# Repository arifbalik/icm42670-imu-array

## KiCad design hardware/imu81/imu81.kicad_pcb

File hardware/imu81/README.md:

# IMU81 Array Module

<div align="center">

</div>

## Overview

A compact 8-sensor IMU array module featuring ICM-42670-P sensors with STM32 microcontroller for high-performance and very high-accuracy motion sensing applications.

## Key Features

### IMU Sensors

- **8x ICM-42670-P** 6-axis MEMS motion tracking devices
- High-performance 3-axis gyroscope and 3-axis accelerometer  
- Shared SPI bus with individual interrupt lines
- **Gyroscope Range**: ±250, ±500, ±1000, ±2000 dps
- **Accelerometer Range**: ±2, ±4, ±8, ±16 g

### Microcontroller

- **STM32U031K8** ARM Cortex-M0+ ultra-low-power MCU
- 64KB Flash memory, 12KB SRAM
- Ultra-low power consumption

### Interface & Connectivity

- **Dual 6-pin headers** for external connections
- SPI interface for sensor communication
- I2C/UART interface for external communication
- One interrupt line for the host
- Interrupt signals from all 8 IMU sensors

## Technical Specifications

### Dimensions

- **Size**: 16mm x 17mm
- **Weight**: 5g

### Power Supply

- **Operating Voltage**: 1.8V - 3.3V
- **Power Consumption**: Ultra-low power design optimized for battery operation

#### Individual Power Consumption

- **ICM-42670-P (Single)**: 0.55mA (active), 3.5µA (sleep)
- **STM32U031K8**: 4mA (active), 16nA (sleep)

## Operating Conditions

- **Temperature Range**: -40°C to +85°C
- **Humidity Range**: 0% to 100% (non-condensing)

## How To Build

To generate fabrication artifacts make sure you have [Docker](https://www.docker.com/) installed and running.

Then simply run;

```bash
make build
```

from the project root. This will generate an `output` directory containing the fabrication artifacts in the parent directory.

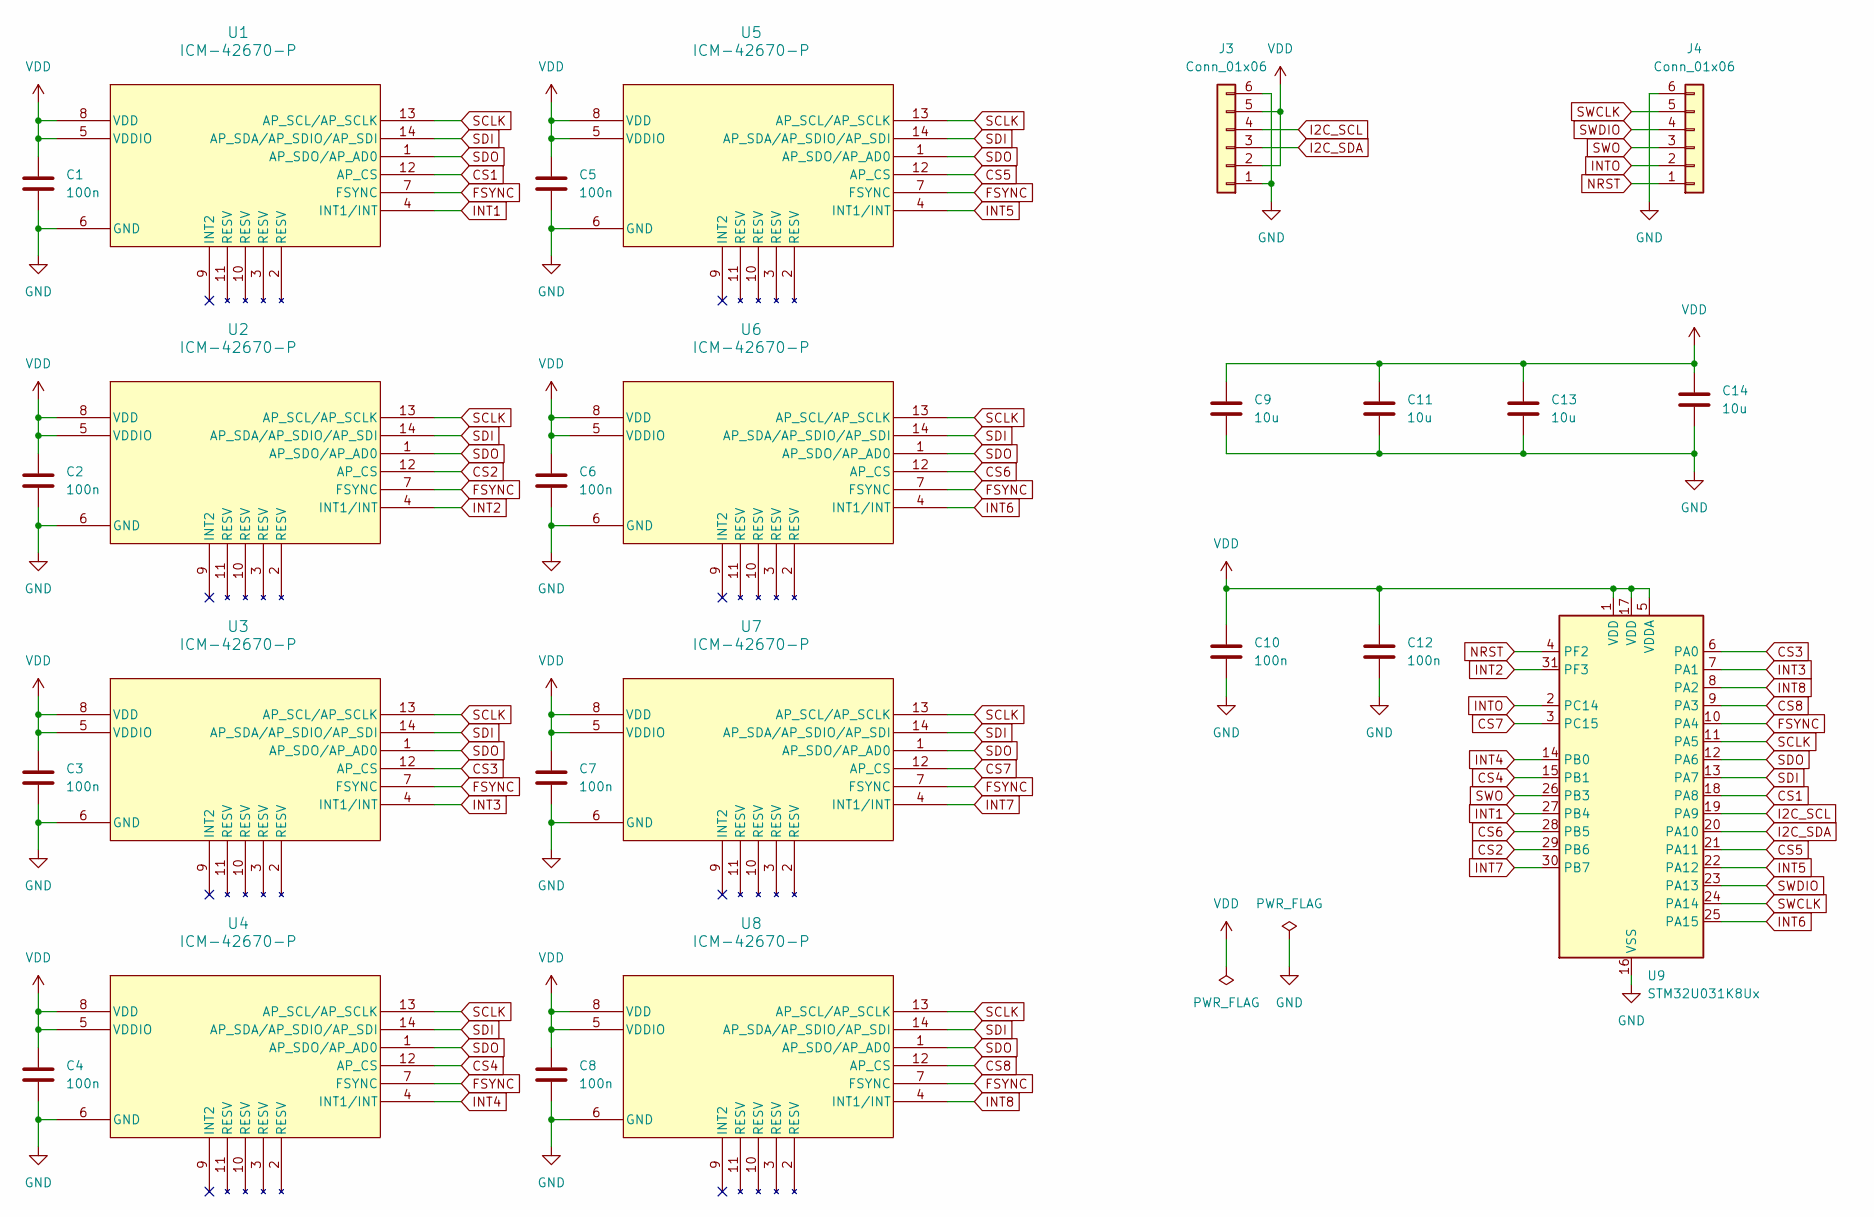
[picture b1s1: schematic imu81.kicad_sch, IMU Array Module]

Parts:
C1, C2, C3, C4, C5, C6, C7, C8, C10, C12: 100n; C_0201_0603Metric
C9, C11, C13, C14: 10u; C_0603_1608Metric
J3, J4: Conn_01x06; PinHeader_1x06_P2.54mm_Vertical
U1, U2, U3, U4, U5, U6, U7, U8: ICM-42670-P; LGA14_2.5X3X0.76_IVS
U9: STM32U031K8Ux; QFN-32-1EP_5x5mm_P0.5mm_EP3.45x3.45mm

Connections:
CS1: U1.12 (AP_CS), U9.18 (PA8)
CS2: U2.12 (AP_CS), U9.29 (PB6)
CS3: U3.12 (AP_CS), U9.6 (PA0)
CS4: U4.12 (AP_CS), U9.15 (PB1)
CS5: U5.12 (AP_CS), U9.21 (PA11)
CS6: U6.12 (AP_CS), U9.28 (PB5)
CS7: U7.12 (AP_CS), U9.3 (PC15)
CS8: U8.12 (AP_CS), U9.9 (PA3)
FSYNC: U1.7 (FSYNC), U2.7 (FSYNC), U3.7 (FSYNC), U4.7 (FSYNC), U5.7 (FSYNC), U6.7 (FSYNC), U7.7 (FSYNC), U8.7 (FSYNC), U9.10 (PA4)
GND: C1.2, C2.2, C3.2, C4.2, C5.2, C6.2, C7.2, C8.2, C9.2, C10.2, C11.2, C12.2, C13.2, C14.2, J3.1, J3.6, J4.6, U1.6 (GND), U2.6 (GND), U3.6 (GND), U4.6 (GND), U5.6 (GND), U6.6 (GND), U7.6 (GND), U8.6 (GND), U9.16 (VSS), U9.32 (VSS), U9.33 (VSS)
I2C_SCL: J3.4, U9.19 (PA9)
I2C_SDA: J3.3, U9.20 (PA10)
INT1: U1.4 (INT1/INT), U9.27 (PB4)
INT2: U2.4 (INT1/INT), U9.31 (PF3)
INT3: U3.4 (INT1/INT), U9.7 (PA1)
INT4: U4.4 (INT1/INT), U9.14 (PB0)
INT5: U5.4 (INT1/INT), U9.22 (PA12)
INT6: U6.4 (INT1/INT), U9.25 (PA15)
INT7: U7.4 (INT1/INT), U9.30 (PB7)
INT8: U8.4 (INT1/INT), U9.8 (PA2)
INTO: J4.2, U9.2 (PC14)
NRST: J4.1, U9.4 (PF2)
SCLK: U1.13 (AP_SCL/AP_SCLK), U2.13 (AP_SCL/AP_SCLK), U3.13 (AP_SCL/AP_SCLK), U4.13 (AP_SCL/AP_SCLK), U5.13 (AP_SCL/AP_SCLK), U6.13 (AP_SCL/AP_SCLK), U7.13 (AP_SCL/AP_SCLK), U8.13 (AP_SCL/AP_SCLK), U9.11 (PA5)
SDI: U1.14 (AP_SDA/AP_SDIO/AP_SDI), U2.14 (AP_SDA/AP_SDIO/AP_SDI), U3.14 (AP_SDA/AP_SDIO/AP_SDI), U4.14 (AP_SDA/AP_SDIO/AP_SDI), U5.14 (AP_SDA/AP_SDIO/AP_SDI), U6.14 (AP_SDA/AP_SDIO/AP_SDI), U7.14 (AP_SDA/AP_SDIO/AP_SDI), U8.14 (AP_SDA/AP_SDIO/AP_SDI), U9.13 (PA7)
SDO: U1.1 (AP_SDO/AP_AD0), U2.1 (AP_SDO/AP_AD0), U3.1 (AP_SDO/AP_AD0), U4.1 (AP_SDO/AP_AD0), U5.1 (AP_SDO/AP_AD0), U6.1 (AP_SDO/AP_AD0), U7.1 (AP_SDO/AP_AD0), U8.1 (AP_SDO/AP_AD0), U9.12 (PA6)
SWCLK: J4.5, U9.24 (PA14)
SWDIO: J4.4, U9.23 (PA13)
SWO: J4.3, U9.26 (PB3)
VDD: C1.1, C2.1, C3.1, C4.1, C5.1, C6.1, C7.1, C8.1, C9.1, C10.1, C11.1, C12.1, C13.1, C14.1, J3.2, J3.5, U1.5 (VDDIO), U1.8 (VDD), U2.5 (VDDIO), U2.8 (VDD), U3.5 (VDDIO), U3.8 (VDD), U4.5 (VDDIO), U4.8 (VDD), U5.5 (VDDIO), U5.8 (VDD), U6.5 (VDDIO), U6.8 (VDD), U7.5 (VDDIO), U7.8 (VDD), U8.5 (VDDIO), U8.8 (VDD), U9.1 (VDD), U9.5 (VDDA), U9.17 (VDD)

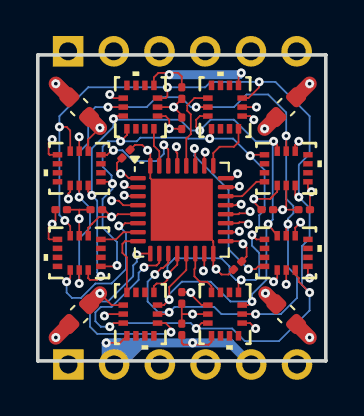
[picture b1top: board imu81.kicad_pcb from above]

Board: 4 copper layers, 16.0 x 17.0 mm, 25 parts (0 on the bottom side), 29 nets.

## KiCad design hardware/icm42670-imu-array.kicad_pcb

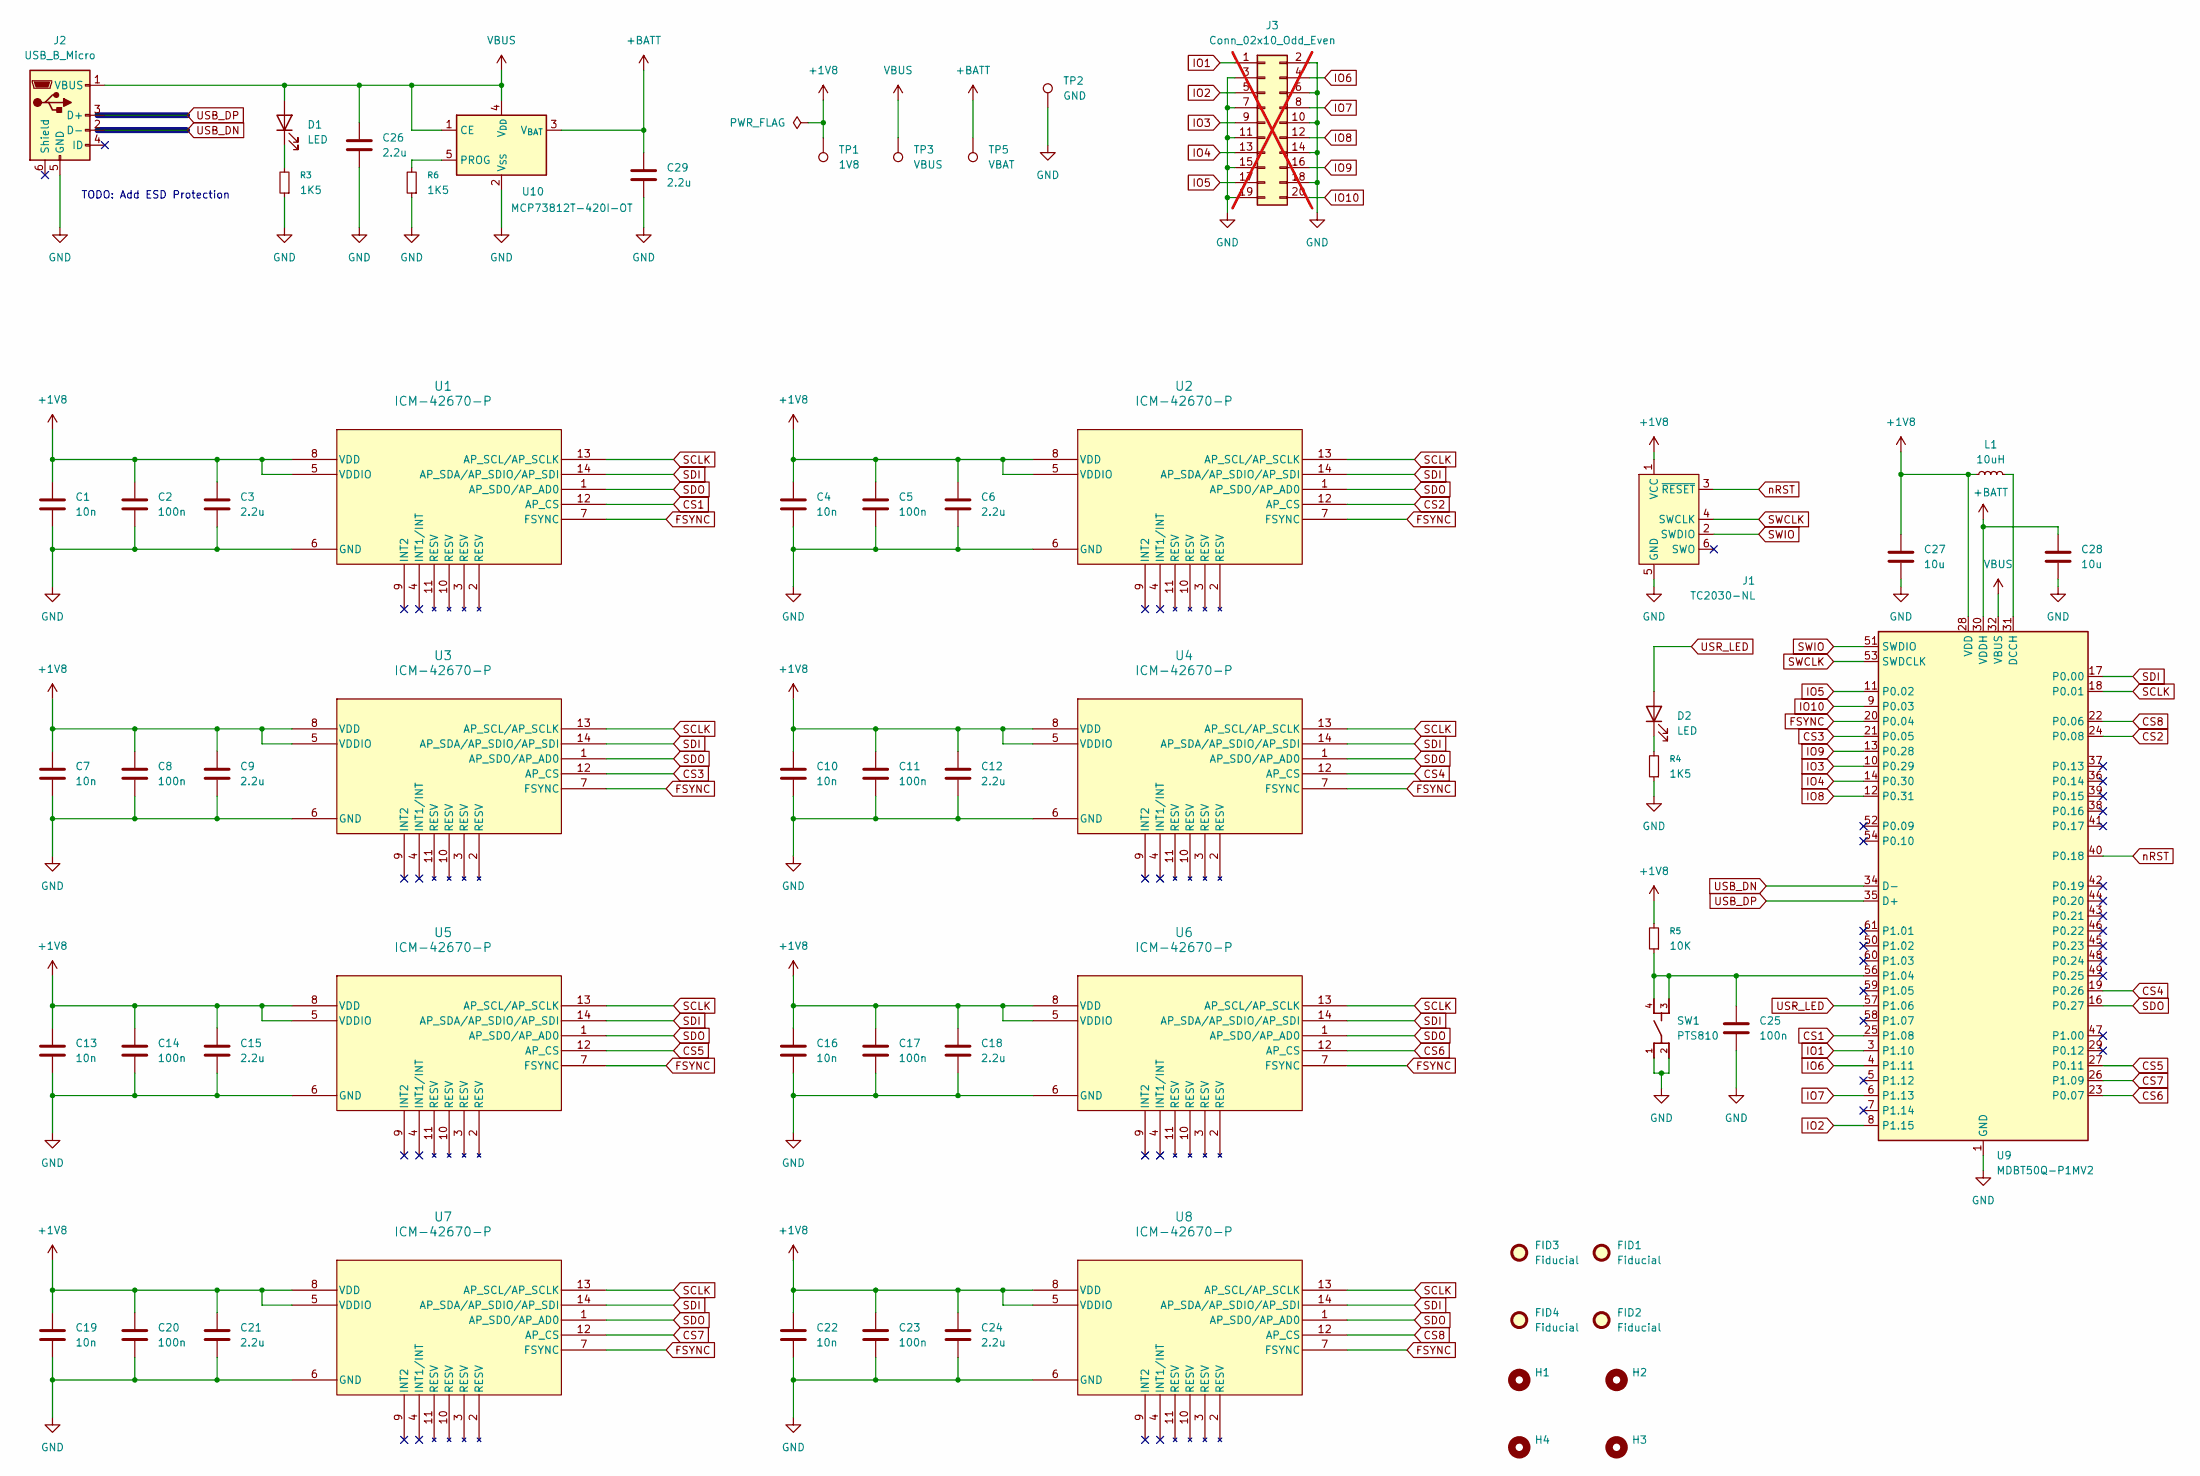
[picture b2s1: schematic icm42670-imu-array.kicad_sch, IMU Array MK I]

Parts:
C1, C4, C7, C10, C13, C16, C19, C22: 10n; C_0603_1608Metric
C2, C5, C8, C11, C14, C17, C20, C23, C25: 100n; C_0603_1608Metric
C3, C6, C9, C12, C15, C18, C21, C24, C26, C29: 2.2u; C_0603_1608Metric
C27, C28: 10u; C_0603_1608Metric
D1, D2: LED; LED_0603_1608Metric
FID1, FID2, FID3, FID4: Fiducial; Fiducial_0.5mm_Mask1.5mm
H1, H2, H3, H4: MountingHole; MountingHole_2.1mm
J1: TC2030-NL; Tag-Connect_TC2030-IDC-NL_2x03_P1.27mm_Vertical
J2: USB_B_Micro; AMPHENOL_10118192-0001LF
J3: Conn_02x10_Odd_Even; PinHeader_2x10_P1.00mm_Vertical_SMD; not fitted
L1: 10uH; L_0603_1608Metric
R3, R4, R6: 1K5; R_0603_1608Metric
R5: 10K; R_0603_1608Metric
SW1: PTS810; SW_PTS810_SJM_250_SMTR_LFS
TP1: 1V8; TestPoint_Pad_D1.0mm
TP2: GND; TestPoint_Pad_D1.0mm
TP3: VBUS; TestPoint_Pad_D1.0mm
TP5: VBAT; TestPoint_Pad_D1.0mm
U1, U2, U3, U4, U5, U6, U7, U8: ICM-42670-P; LGA14_2.5X3X0.76_IVS
U9: MDBT50Q-P1MV2; Raytac_MDBT50Q
U10: MCP73812T-420I-OT; SOT-23-5

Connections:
+1V8: C1.1, C2.1, C3.1, C4.1, C5.1, C6.1, C7.1, C8.1, C9.1, C10.1, C11.1, C12.1, C13.1, C14.1, C15.1, C16.1, C17.1, C18.1, C19.1, C20.1, C21.1, C22.1, C23.1, C24.1, C27.1, J1.1 (VCC), L1.1, R5.2, TP1.1, U1.5 (VDDIO), U1.8 (VDD), U2.5 (VDDIO), U2.8 (VDD), U3.5 (VDDIO), U3.8 (VDD), U4.5 (VDDIO), U4.8 (VDD), U5.5 (VDDIO), U5.8 (VDD), U6.5 (VDDIO), U6.8 (VDD), U7.5 (VDDIO), U7.8 (VDD), U8.5 (VDDIO), U8.8 (VDD), U9.28 (VDD)
CS1: U1.12 (AP_CS), U9.25 (P1.08)
CS2: U2.12 (AP_CS), U9.24 (P0.08)
CS3: U3.12 (AP_CS), U9.21 (P0.05)
CS4: U4.12 (AP_CS), U9.19 (P0.26)
CS5: U5.12 (AP_CS), U9.27 (P0.11)
CS6: U6.12 (AP_CS), U9.23 (P0.07)
CS7: U7.12 (AP_CS), U9.26 (P1.09)
CS8: U8.12 (AP_CS), U9.22 (P0.06)
FSYNC: U1.7 (FSYNC), U2.7 (FSYNC), U3.7 (FSYNC), U4.7 (FSYNC), U5.7 (FSYNC), U6.7 (FSYNC), U7.7 (FSYNC), U8.7 (FSYNC), U9.20 (P0.04)
GND: C1.2, C2.2, C3.2, C4.2, C5.2, C6.2, C7.2, C8.2, C9.2, C10.2, C11.2, C12.2, C13.2, C14.2, C15.2, C16.2, C17.2, C18.2, C19.2, C20.2, C21.2, C22.2, C23.2, C24.2, C25.2, C26.2, C27.2, C28.2, C29.2, J1.5 (GND), J2.5 (GND), J3.2, J3.3, J3.6, J3.7, J3.10, J3.11, J3.14, J3.15, J3.18, J3.19, R3.1, R4.1, R6.1, SW1.1, SW1.2, TP2.1, U1.6 (GND), U2.6 (GND), U3.6 (GND), U4.6 (GND), U5.6 (GND), U6.6 (GND), U7.6 (GND), U8.6 (GND), U9.1 (GND), U9.2 (GND), U9.15 (GND), U9.33 (GND), U9.55 (GND), U10.2 (V_{SS})
IO1: J3.1, U9.3 (P1.10)
IO2: J3.5, U9.8 (P1.15)
IO3: J3.9, U9.10 (P0.29)
IO4: J3.13, U9.14 (P0.30)
IO5: J3.17, U9.11 (P0.02)
IO6: J3.4, U9.4 (P1.11)
IO7: J3.8, U9.6 (P1.13)
IO8: J3.12, U9.12 (P0.31)
IO9: J3.16, U9.13 (P0.28)
IO10: J3.20, U9.9 (P0.03)
unnamed: D1.1 (K), R3.2
unnamed: D2.1 (K), R4.2
unnamed: L1.2, U9.31 (DCCH)
unnamed: C25.1, R5.1, SW1.3, SW1.4, U9.56 (P1.04)
unnamed: R6.2, U10.5 (PROG)
SCLK: U1.13 (AP_SCL/AP_SCLK), U2.13 (AP_SCL/AP_SCLK), U3.13 (AP_SCL/AP_SCLK), U4.13 (AP_SCL/AP_SCLK), U5.13 (AP_SCL/AP_SCLK), U6.13 (AP_SCL/AP_SCLK), U7.13 (AP_SCL/AP_SCLK), U8.13 (AP_SCL/AP_SCLK), U9.18 (P0.01)
SDI: U1.14 (AP_SDA/AP_SDIO/AP_SDI), U2.14 (AP_SDA/AP_SDIO/AP_SDI), U3.14 (AP_SDA/AP_SDIO/AP_SDI), U4.14 (AP_SDA/AP_SDIO/AP_SDI), U5.14 (AP_SDA/AP_SDIO/AP_SDI), U6.14 (AP_SDA/AP_SDIO/AP_SDI), U7.14 (AP_SDA/AP_SDIO/AP_SDI), U8.14 (AP_SDA/AP_SDIO/AP_SDI), U9.17 (P0.00)
SDO: U1.1 (AP_SDO/AP_AD0), U2.1 (AP_SDO/AP_AD0), U3.1 (AP_SDO/AP_AD0), U4.1 (AP_SDO/AP_AD0), U5.1 (AP_SDO/AP_AD0), U6.1 (AP_SDO/AP_AD0), U7.1 (AP_SDO/AP_AD0), U8.1 (AP_SDO/AP_AD0), U9.16 (P0.27)
SWCLK: J1.4 (SWCLK), U9.53 (SWDCLK)
SWIO: J1.2 (SWDIO), U9.51 (SWDIO)
USB_DN: J2.2 (D-), U9.34 (D-)
USB_DP: J2.3 (D+), U9.35 (D+)
USR_LED: D2.2 (A), U9.57 (P1.06)
VBUS: C26.1, D1.2 (A), J2.1 (VBUS), TP3.1, U9.32 (VBUS), U10.1 (CE), U10.4 (V_{DD}); also elsewhere on the board
nRST: J1.3 (~RESET), U9.40 (P0.18)

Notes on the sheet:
TODO: Add ESD Protection

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
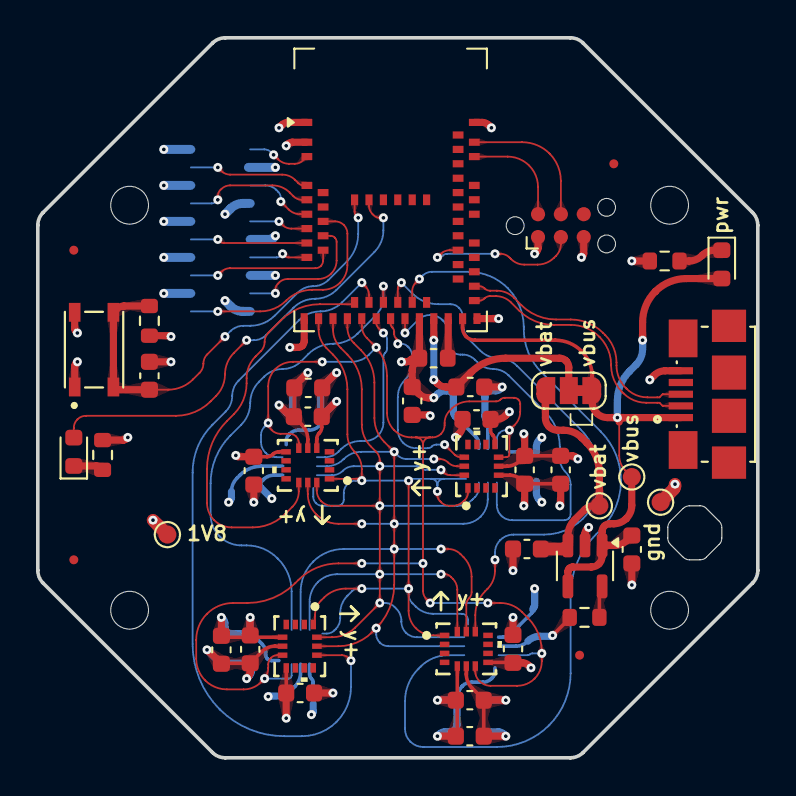
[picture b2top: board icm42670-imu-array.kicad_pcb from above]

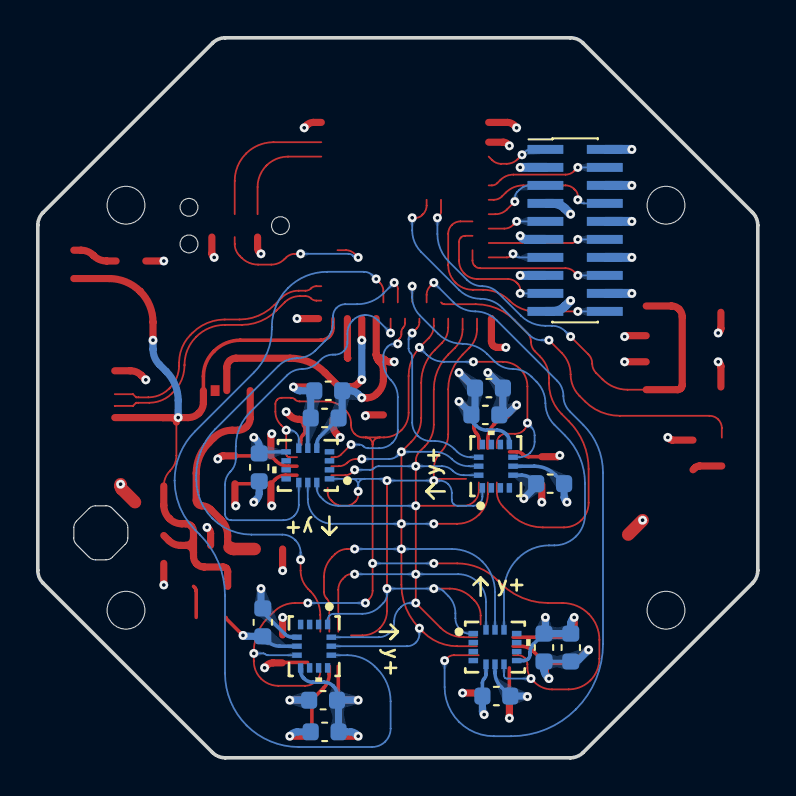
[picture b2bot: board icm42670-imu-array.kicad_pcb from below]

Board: 4 copper layers, 40.0 x 40.0 mm, 63 parts (17 on the bottom side), 38 nets.

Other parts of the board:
JP2: Voltage Selector; SolderJumper-3_P1.3mm_Bridged12_RoundedPad1.0x1.5mm

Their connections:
VBUS: JP2.1 (A); also elsewhere on the board

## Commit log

2025-08-17 feat: initial pcb
2025-08-17 docs: update readme
2025-08-17 feat: add round tracks
2025-08-22 feat: add imu81
2025-08-23 feat: add workflow
2025-08-23 chore: update artifact retention time
2025-08-23 docs: update readmes
2025-08-23 feat: add blender renders
